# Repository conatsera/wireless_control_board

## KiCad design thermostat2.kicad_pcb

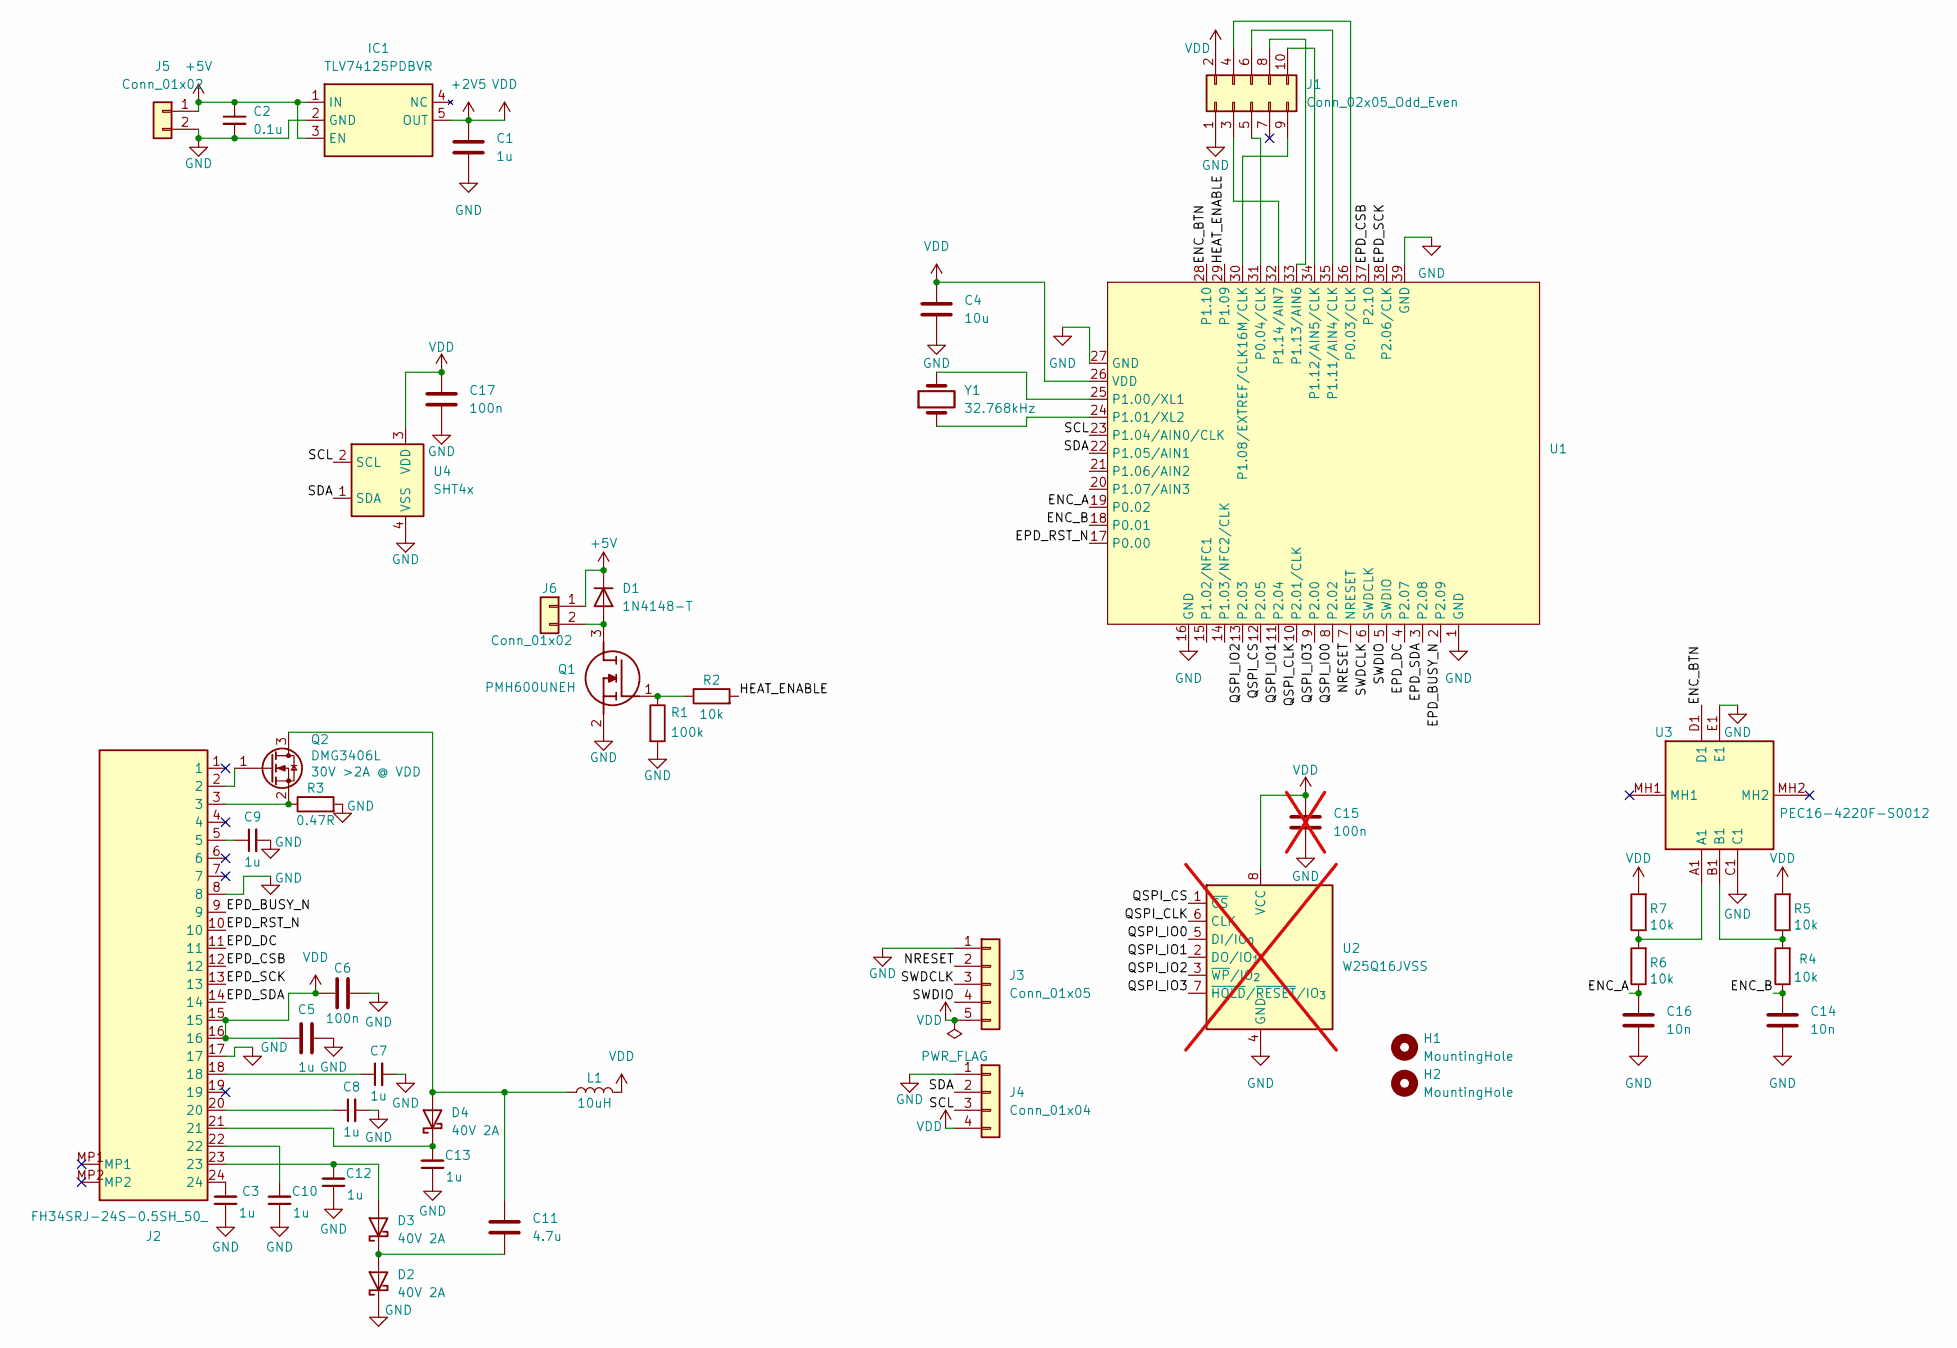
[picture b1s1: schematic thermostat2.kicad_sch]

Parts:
C1, C5: 1u; C_0402_1005Metric
C2: 0.1u; C_0402_1005Metric
C3, C7, C8, C9, C10, C12, C13: 1u; C_0603_1608Metric
C4: 10u; C_0603_1608Metric
C6, C17: 100n; C_0402_1005Metric
C11: 4.7u; C_0805_2012Metric
C14, C16: 10n; C_0402_1005Metric
C15: 100n; C_0402_1005Metric; not fitted
D1: 1N4148-T; D_DO-35_SOD27_P2.54mm_Vertical_AnodeUp
D2, D3, D4: 40V 2A; SODFL3618X110N
H1, H2: MountingHole; MountingHole_2.2mm_M2
IC1: TLV74125PDBVR; SOT95P280X145-5N; Mouser Part Number 595-TLV74125PDBVR
J1: Conn_02x05_Odd_Even; PinHeader_2x05_P2.54mm_Vertical_SMD
J2: FH34SRJ-24S-0.5SH_50_; FH34SRJ24S05SH50; Mouser Part Number 798-FH34SRJ24S05SH50
J3: Conn_01x05; PinHeader_1x05_P1.27mm_Vertical
J4: Conn_01x04; PinHeader_1x04_P1.27mm_Vertical
J5, J6: Conn_01x02; PinHeader_1x02_P2.54mm_Vertical
L1: 10uH; ATNR4010
Q1: PMH600UNEH; Mouser Part Number 771-PMH600UNEH
Q2: DMG3406L; SOT-23-3
R1: 100k; R_0603_1608Metric
R2, R4, R5, R6, R7: 10k; R_0603_1608Metric
R3: 0.47R; R_0402_1005Metric
U1: 453-00xxx
U2: W25Q16JVSS; SOIC-8_5.3x5.3mm_P1.27mm; not fitted
U3: PEC16-4220F-S0012; PEC164120FS0012; Manufacturer_Part_Number PEC16-4220F-S0024; Mouser Part Number 652-PEC16-4220FS0024
U4: SHT4x; Sensirion_DFN-4_1.5x1.5mm_P0.8mm_SHT4x_NoCentralPad
Y1: 32.768kHz; Crystal_SMD_2012-2Pin_2.0x1.2mm

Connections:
+2V5: C1.1, C4.1, C5.1, C6.1, C15.1, C17.1, IC1.5 (OUT), J1.2, J2.15, J2.16, J3.5, J4.4, L1.2, R5.2, R7.2, U1.26 (VDD), U2.8 (VCC), U4.3 (VDD)
+5V: C2.1, D1.1 (K), IC1.1 (IN), IC1.3 (EN), J5.1, J6.1
/ENC_A: C16.1, R6.1, U1.19 (P0.02)
/ENC_B: C14.1, R4.1, U1.18 (P0.01)
/ENC_BTN: U1.28 (P1.10), U3.D1
/EPD_BUSY_N: J2.9, U1.2 (P2.09)
/EPD_CSB: J2.12, U1.37 (P2.10)
/EPD_DC: J2.11, U1.4 (P2.07)
/EPD_RST_N: J2.10, U1.17 (P0.00)
/EPD_SCK: J2.13, U1.38 (P2.06/CLK)
/EPD_SDA: J2.14, U1.3 (P2.08)
/HEAT_ENABLE: R2.2, U1.29 (P1.09)
/NRESET: J3.2, U1.7 (NRESET)
/QSPI_CLK: U1.10 (P2.01/CLK), U2.6 (CLK)
/QSPI_CS: U1.12 (P2.05), U2.1 (~CS)
/QSPI_IO0: U1.8 (P2.02), U2.5 (DI/IO_{0})
/QSPI_IO1: U1.11 (P2.04), U2.2 (DO/IO_{1})
/QSPI_IO2: U1.13 (P2.03), U2.3 (~WP/IO_{2})
/QSPI_IO3: U1.9 (P2.00), U2.7 (~HOLD/~RESET/IO_{3})
/SCL: J4.3, U1.23 (P1.04/AIN0/CLK), U4.2 (SCL)
/SDA: J4.2, U1.22 (P1.05/AIN1), U4.1 (SDA)
/SWDCLK: J3.3, U1.6 (SWDCLK)
/SWDIO: J3.4, U1.5 (SWDIO)
GND: C1.2, C2.2, C3.1, C4.2, C5.2, C6.2, C7.2, C8.2, C9.2, C10.1, C12.1, C13.1, C14.2, C15.2, C16.2, C17.2, D2.1 (K), IC1.2 (GND), J1.1, J2.8, J2.17, J3.1, J4.1, J5.2, Q1.2 (S), R1.2, R3.2, U1.1 (GND), U1.16 (GND), U1.27 (GND), U1.39 (GND), U2.4 (GND), U3.C1, U3.E1, U4.4 (VSS)
unnamed: C3.2, J2.24
unnamed: C7.1, J2.18
unnamed: C8.1, J2.20
unnamed: C9.1, J2.5
unnamed: C10.2, J2.22
unnamed: D1.2 (A), J6.2, Q1.3 (D)
unnamed: C11.2, D2.2 (A), D3.1 (K)
unnamed: C12.2, D3.2 (A), J2.23
unnamed: C11.1, D4.2 (A), L1.1, Q2.3 (D)
unnamed: C13.2, D4.1 (K), J2.21
unnamed: J1.3, U1.32 (P1.14/AIN7)
unnamed: J1.4, U1.36 (P0.03/CLK)
unnamed: J1.5, U1.31 (P0.04/CLK)
unnamed: J1.6, U1.35 (P1.11/AIN4/CLK)
unnamed: J1.8, U1.33 (P1.13/AIN6)
unnamed: J1.9, U1.30 (P1.08/EXTREF/CLK16M/CLK)
unnamed: J1.10, U1.34 (P1.12/AIN5/CLK)
unnamed: Q1.1 (G), R1.1, R2.1
unnamed: J2.2, Q2.1 (G)
unnamed: J2.3, Q2.2 (S), R3.1
unnamed: R4.2, R5.1, U3.B1
unnamed: R6.2, R7.1, U3.A1
unnamed: U1.25 (P1.00/XL1), Y1.2
unnamed: U1.24 (P1.01/XL2), Y1.1

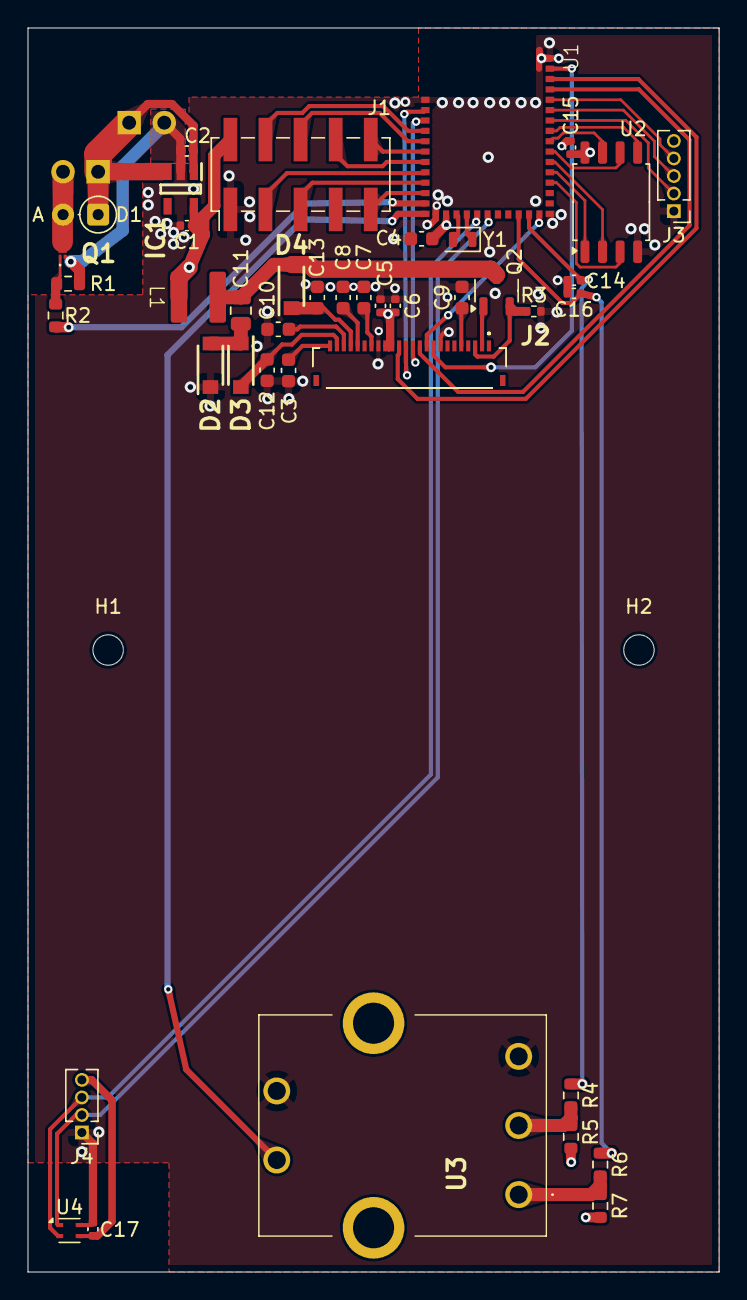
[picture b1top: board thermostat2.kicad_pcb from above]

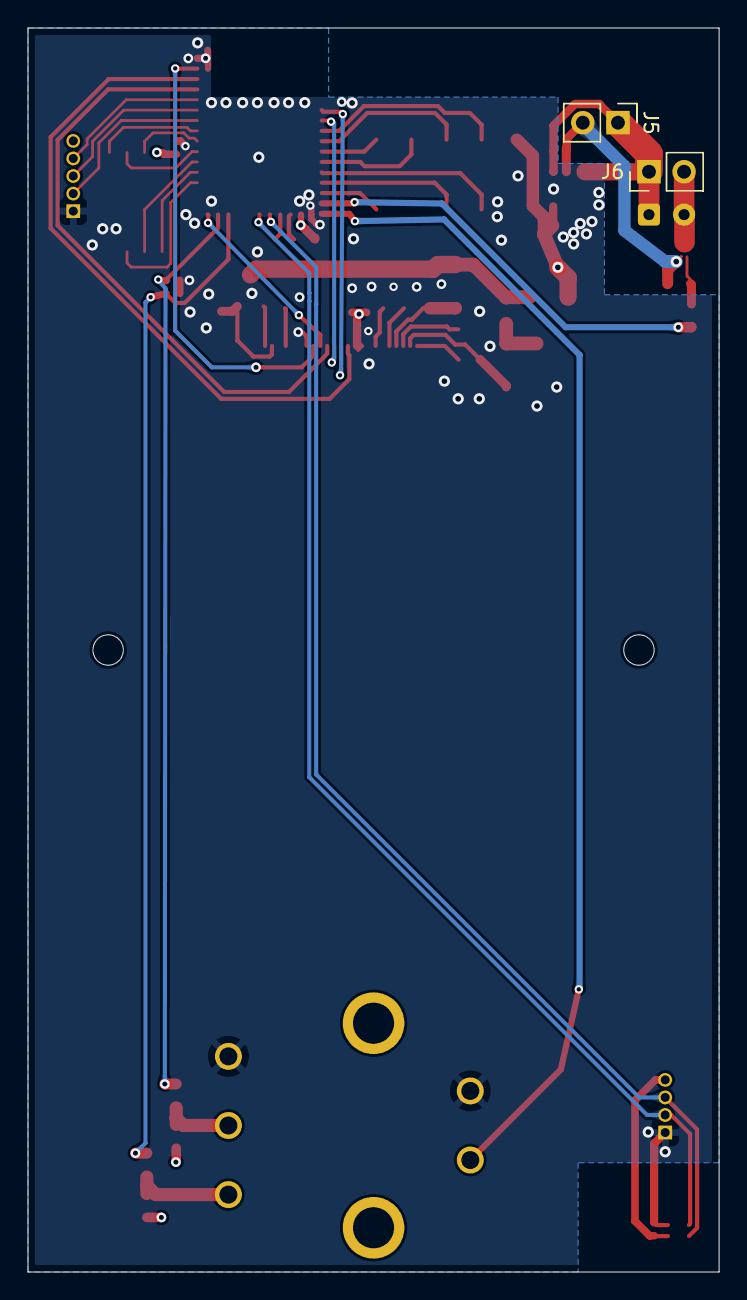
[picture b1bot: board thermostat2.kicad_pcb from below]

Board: 4 copper layers, 50.0 x 90.0 mm, 45 parts (2 on the bottom side), 48 nets.

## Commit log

2025-06-12 Create LICENSE
2025-06-12 init commit
